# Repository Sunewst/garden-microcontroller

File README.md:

## Check the ESP32 C6 branch for the most up to date version

### Garden Microcontroller Arduino Library and Board https://github.com/Sunewst/garden-microcontroller-arduino

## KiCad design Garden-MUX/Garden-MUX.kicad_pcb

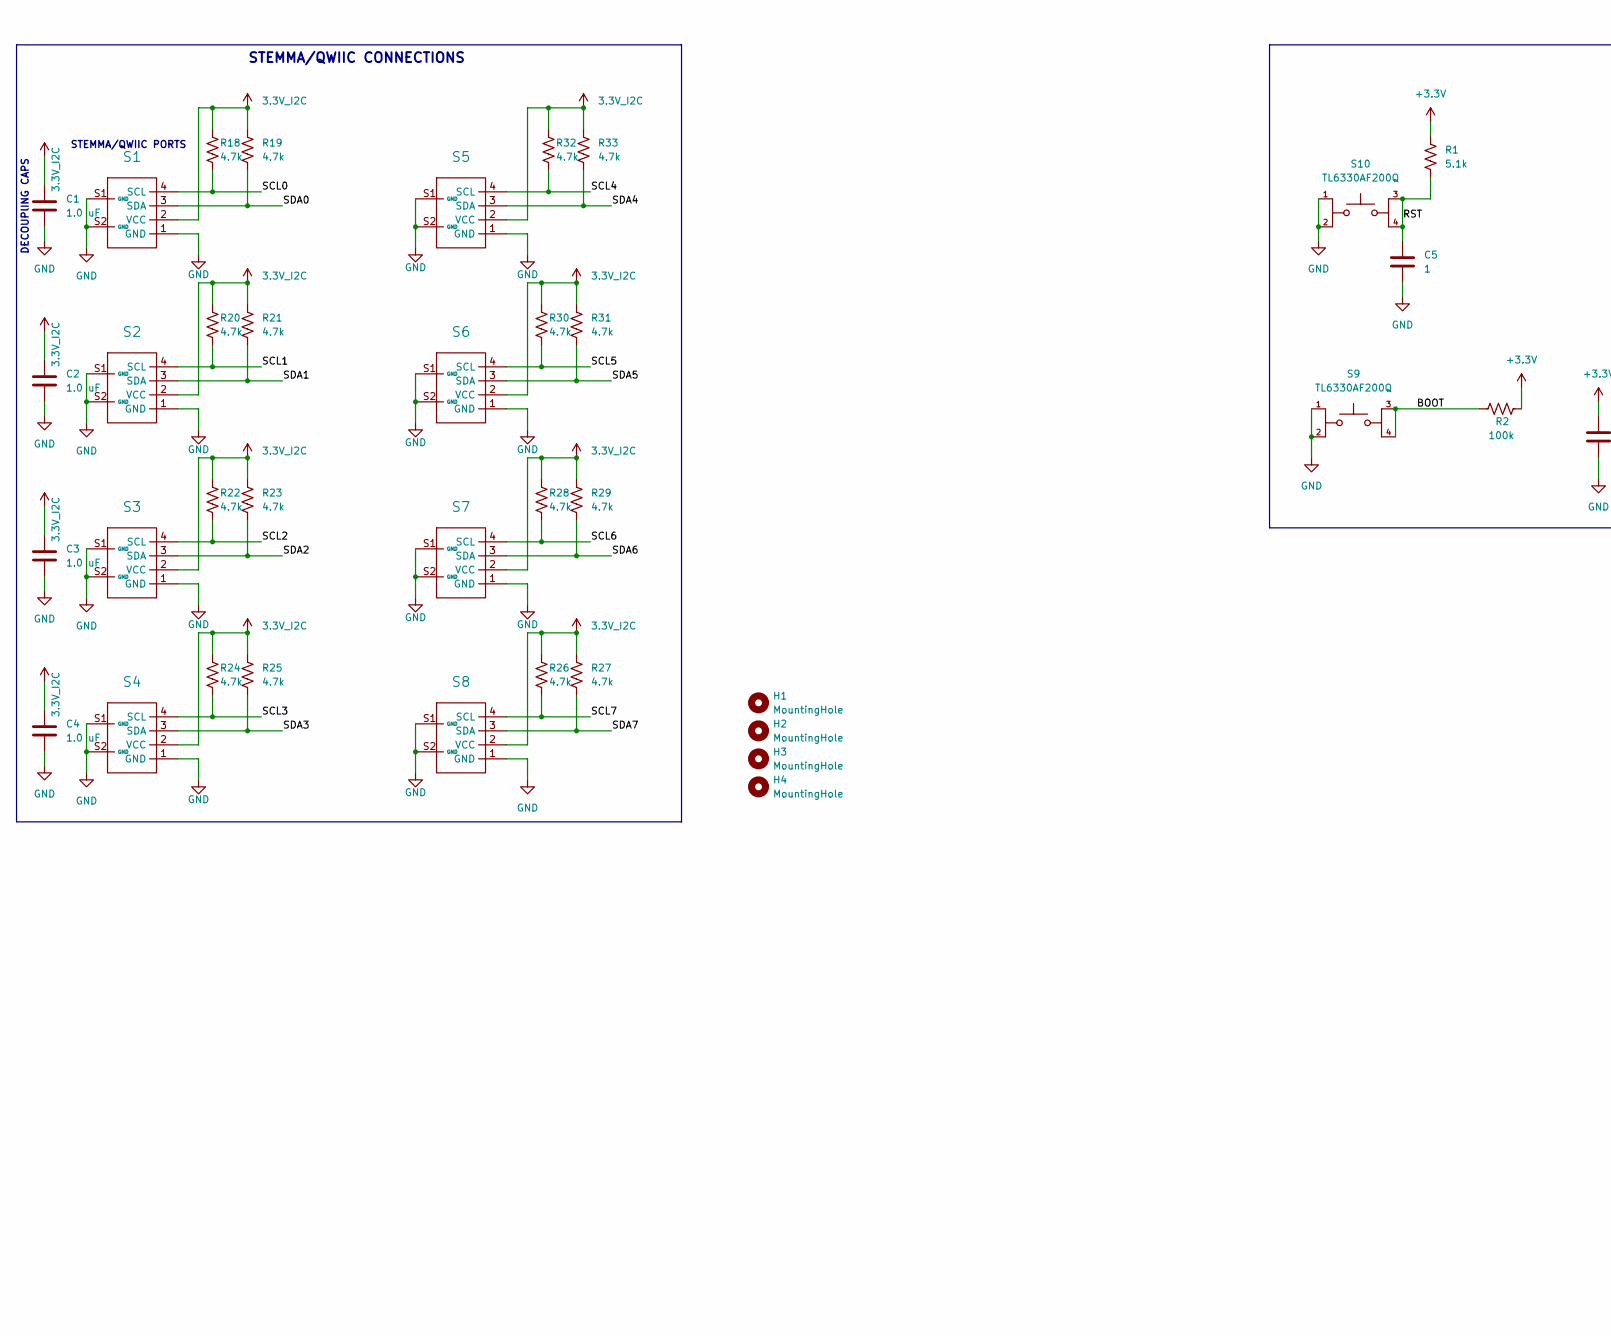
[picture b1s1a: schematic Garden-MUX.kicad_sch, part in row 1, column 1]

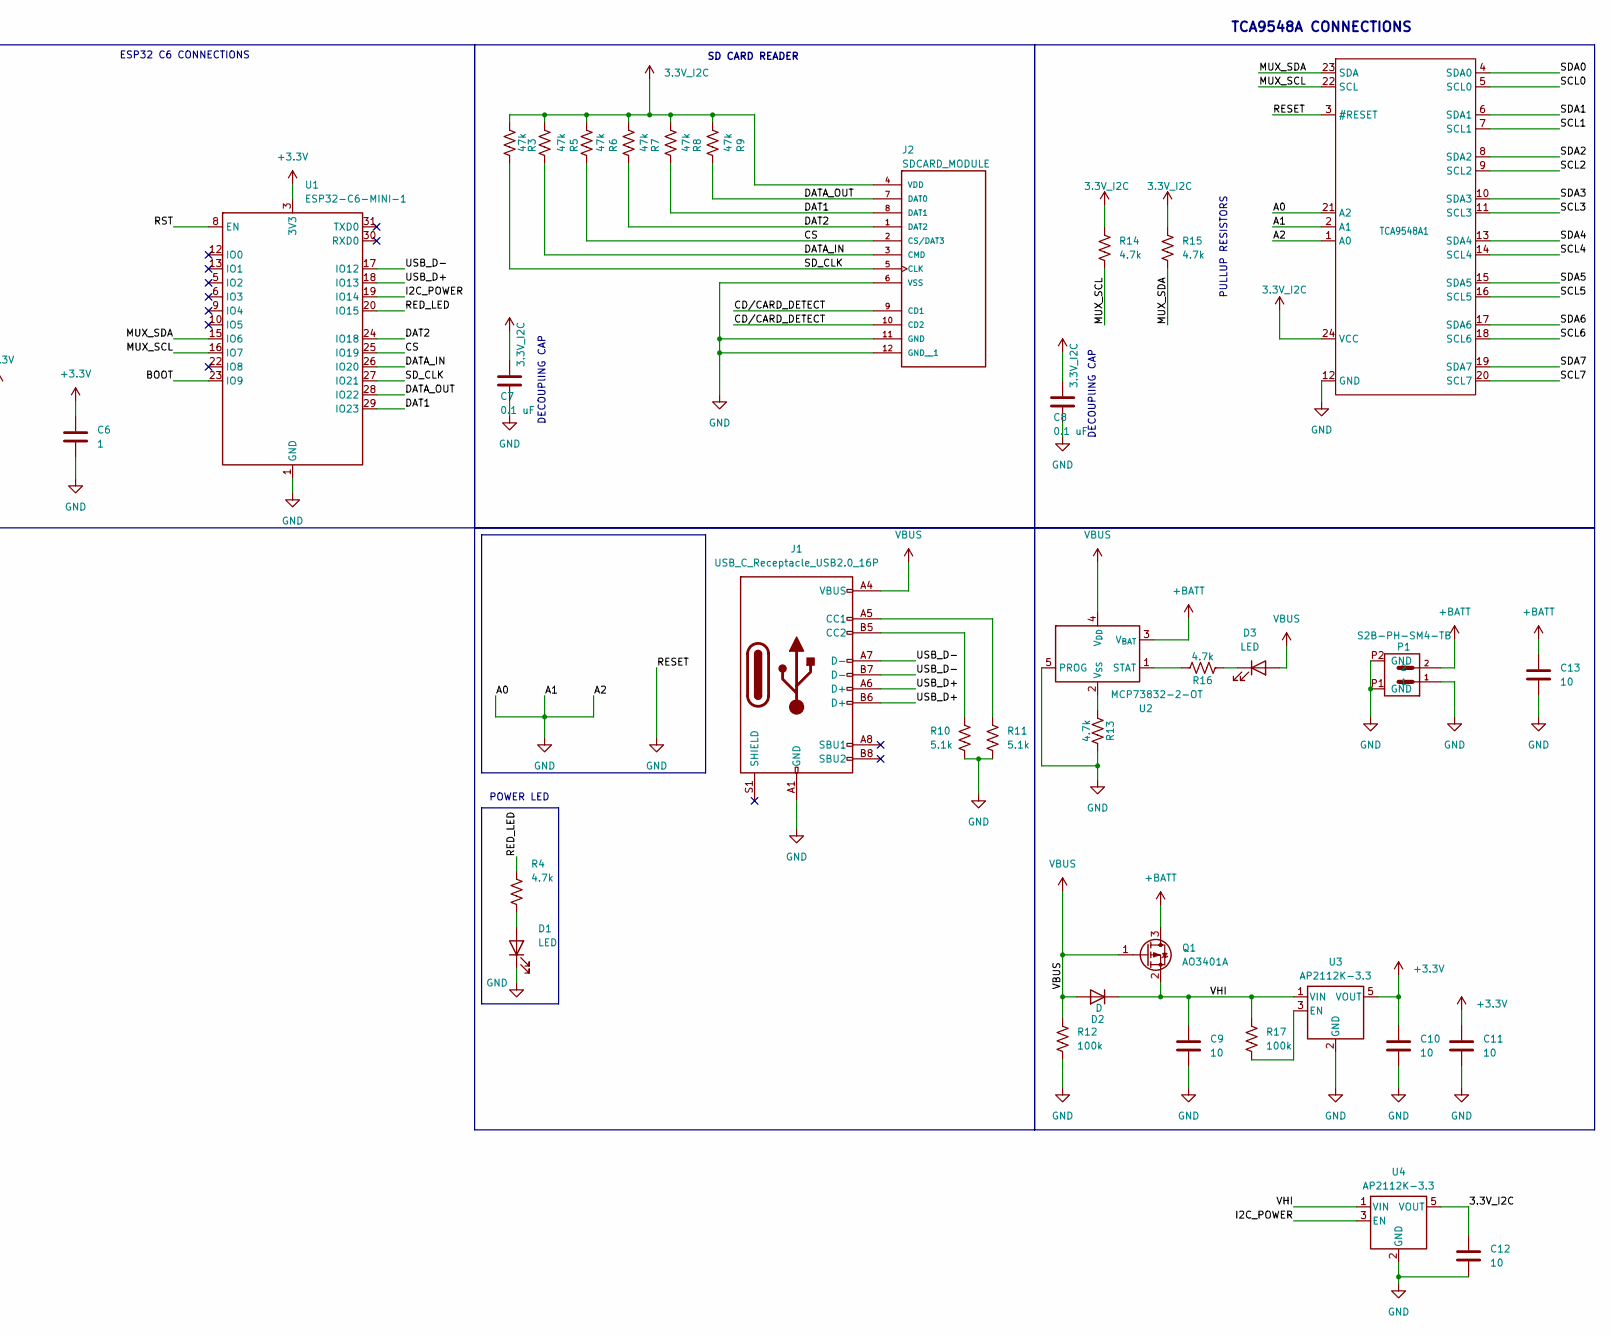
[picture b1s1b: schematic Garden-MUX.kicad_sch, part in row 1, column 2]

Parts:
C1, C2, C3, C4: 1.0 uF; C_0603_1608Metric
C5, C6: 1; C_0603_1608Metric
C7, C8: 0.1 uF; C_0603_1608Metric
C9, C10, C11, C12, C13: 10; C_0603_1608Metric
D1, D3: LED; LED_0603_1608Metric
D2: D; D_0402_1005Metric_Pad0.77x0.64mm_HandSolder
H1, H2, H3, H4: MountingHole; MountingHole_2.5mm
J1: USB_C_Receptacle_USB2.0_16P; USB_C_Receptacle_G-Switch_GT-USB-7010ASV
J2: SDCARD_MODULE; SDCARD_MODULE_Footprint
P1: S2B-PH-SM4-TB; JST_S2B-PH-SM4-TB
Q1: AO3401A; SOT-23
R1, R10, R11: 5.1k; R_0603_1608Metric
R2: 100k; R_0603_1608Metric
R3, R5, R6, R7, R8, R9: 47k; R_0603_1608Metric
R4, R13, R14, R15, R16, R18, R19, R20, R21, R22, R23, R24, R25, R26, R27, R28, R29, R30, R31, R32, R33: 4.7k; R_0603_1608Metric
R12, R17: 100k; R_0805_2012Metric
S1, S2, S3, S4, S5, S6, S7, S8: STEMMAQWIIC_Footprint
S9, S10: TL6330AF200Q; SW_TL6330AF200Q_Footprint; PARTREV D
TCA9548A1: TCA9548A_Footprint
U1: ESP32-C6-MINI-1
U2: MCP73832-2-OT; SOT-23-5
U3, U4: AP2112K-3.3; SOT-23-5

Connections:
3.3V_I2C: C1.1, C2.1, C3.1, C4.1, C7.1, C8.1, C12.1, J2.4 (VDD), R3.1, R5.1, R6.1, R7.1, R8.1, R9.1, R14.1, R15.1, R18.1, R19.1, R20.1, R21.1, R22.1, R23.1, R24.1, R25.1, R26.1, R27.1, R28.1, R29.1, R30.1, R31.1, R32.1, R33.1, S1.2 (VCC), S2.2 (VCC), S3.2 (VCC), S4.2 (VCC), S5.2 (VCC), S6.2 (VCC), S7.2 (VCC), S8.2 (VCC), TCA9548A1.24 (VCC), U4.5 (VOUT)
+3.3V: C6.1, C10.1, C11.1, R1.1, R2.1, U1.3 (3V3), U3.5 (VOUT)
+BATT: C13.1, P1.2, Q1.3 (D), U2.3 (V_{BAT})
/BOOT: R2.2, S9.3, S9.4, U1.23 (IO9)
/CD/CARD_DETECT: J2.9 (CD1), J2.10 (CD2)
/CS: J2.2 (CS/DAT3), R6.2, U1.25 (IO19)
/DAT1: J2.8 (DAT1), R8.2, U1.29 (IO23)
/DAT2: J2.1 (DAT2), R7.2, U1.24 (IO18)
/DATA_IN: J2.3 (CMD), R5.2, U1.26 (IO20)
/DATA_OUT: J2.7 (DAT0), R9.2, U1.28 (IO22)
/I2C_POWER: U1.19 (IO14), U4.3 (EN)
/MUX_SCL: R14.2, TCA9548A1.22 (SCL), U1.16 (IO7)
/MUX_SDA: R15.2, TCA9548A1.23 (SDA), U1.15 (IO6)
/RED_LED: R4.1, U1.20 (IO15)
/RST: C5.1, R1.2, S10.3, S10.4, U1.8 (EN)
/SCL0: R18.2, S1.4 (SCL), TCA9548A1.5 (SCL0)
/SCL1: R20.2, S2.4 (SCL), TCA9548A1.7 (SCL1)
/SCL2: R22.2, S3.4 (SCL), TCA9548A1.9 (SCL2)
/SCL3: R24.2, S4.4 (SCL), TCA9548A1.11 (SCL3)
/SCL4: R32.2, S5.4 (SCL), TCA9548A1.14 (SCL4)
/SCL5: R30.2, S6.4 (SCL), TCA9548A1.16 (SCL5)
/SCL6: R28.2, S7.4 (SCL), TCA9548A1.18 (SCL6)
/SCL7: R26.2, S8.4 (SCL), TCA9548A1.20 (SCL7)
/SDA0: R19.2, S1.3 (SDA), TCA9548A1.4 (SDA0)
/SDA1: R21.2, S2.3 (SDA), TCA9548A1.6 (SDA1)
/SDA2: R23.2, S3.3 (SDA), TCA9548A1.8 (SDA2)
/SDA3: R25.2, S4.3 (SDA), TCA9548A1.10 (SDA3)
/SDA4: R33.2, S5.3 (SDA), TCA9548A1.13 (SDA4)
/SDA5: R31.2, S6.3 (SDA), TCA9548A1.15 (SDA5)
/SDA6: R29.2, S7.3 (SDA), TCA9548A1.17 (SDA6)
/SDA7: R27.2, S8.3 (SDA), TCA9548A1.19 (SDA7)
/SD_CLK: J2.5 (CLK), R3.2, U1.27 (IO21)
/USB_D+: J1.A6 (D+), J1.B6 (D+), U1.18 (IO13)
/USB_D-: J1.A7 (D-), J1.B7 (D-), U1.17 (IO12)
/VHI: C9.1, D2.1 (K), Q1.2 (S), R17.1, U3.1 (VIN), U4.1 (VIN)
GND: C1.2, C2.2, C3.2, C4.2, C5.2, C6.2, C7.2, C8.2, C9.2, C10.2, C11.2, C12.2, C13.2, D1.1 (K), J1.A1 (GND), J1.A12 (GND), J1.B1 (GND), J1.B12 (GND), J2.6 (VSS), J2.11 (GND), J2.12 (GND__1), P1.1, P1.P1 (GND), P1.P2 (GND), R10.2, R11.2, R12.2, R13.1, S1.1 (GND), S1.S1 (GND), S1.S2 (GND), S2.1 (GND), S2.S1 (GND), S2.S2 (GND), S3.1 (GND), S3.S1 (GND), S3.S2 (GND), S4.1 (GND), S4.S1 (GND), S4.S2 (GND), S5.1 (GND), S5.S1 (GND), S5.S2 (GND), S6.1 (GND), S6.S1 (GND), S6.S2 (GND), S7.1 (GND), S7.S1 (GND), S7.S2 (GND), S8.1 (GND), S8.S1 (GND), S8.S2 (GND), S9.1, S9.2, S10.1, S10.2, TCA9548A1.1 (A0), TCA9548A1.2 (A1), TCA9548A1.3 (#RESET), TCA9548A1.12 (GND), TCA9548A1.21 (A2), U1.1 (GND), U1.2 (GND), U1.11 (GND), U1.14 (GND), U1.36 (GND), U1.37 (GND), U1.38 (GND), U1.39 (GND), U1.40 (GND), U1.41 (GND), U1.42 (GND), U1.43 (GND), U1.44 (GND), U1.45 (GND), U1.46 (GND), U1.47 (GND), U1.48 (GND), U1.49 (GND), U1.50 (GND), U1.51 (GND), U1.52 (GND), U1.53 (GND), U2.5 (PROG), U3.2 (GND), U4.2 (GND)
unnamed: D1.2 (A), R4.2
unnamed: D3.1 (K), R16.2
unnamed: J1.A5 (CC1), R11.1
unnamed: J1.B5 (CC2), R10.1
unnamed: R16.1, U2.1 (STAT)
unnamed: R13.2, U2.2 (V_{SS})
unnamed: R17.2, U3.3 (EN)
VBUS: D2.2 (A), D3.2 (A), J1.A4 (VBUS), J1.A9 (VBUS), J1.B4 (VBUS), J1.B9 (VBUS), Q1.1 (G), R12.1, U2.4 (V_{DD})

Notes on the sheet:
POWER LED
STEMMA/QWIIC CONNECTIONS
PULLUP RESISTORS
STEMMA/QWIIC PORTS
SD CARD READER
DECOUPlING CAPS
DECOUPlING CAP
ESP32 C6 CONNECTIONS
TCA9548A CONNECTIONS

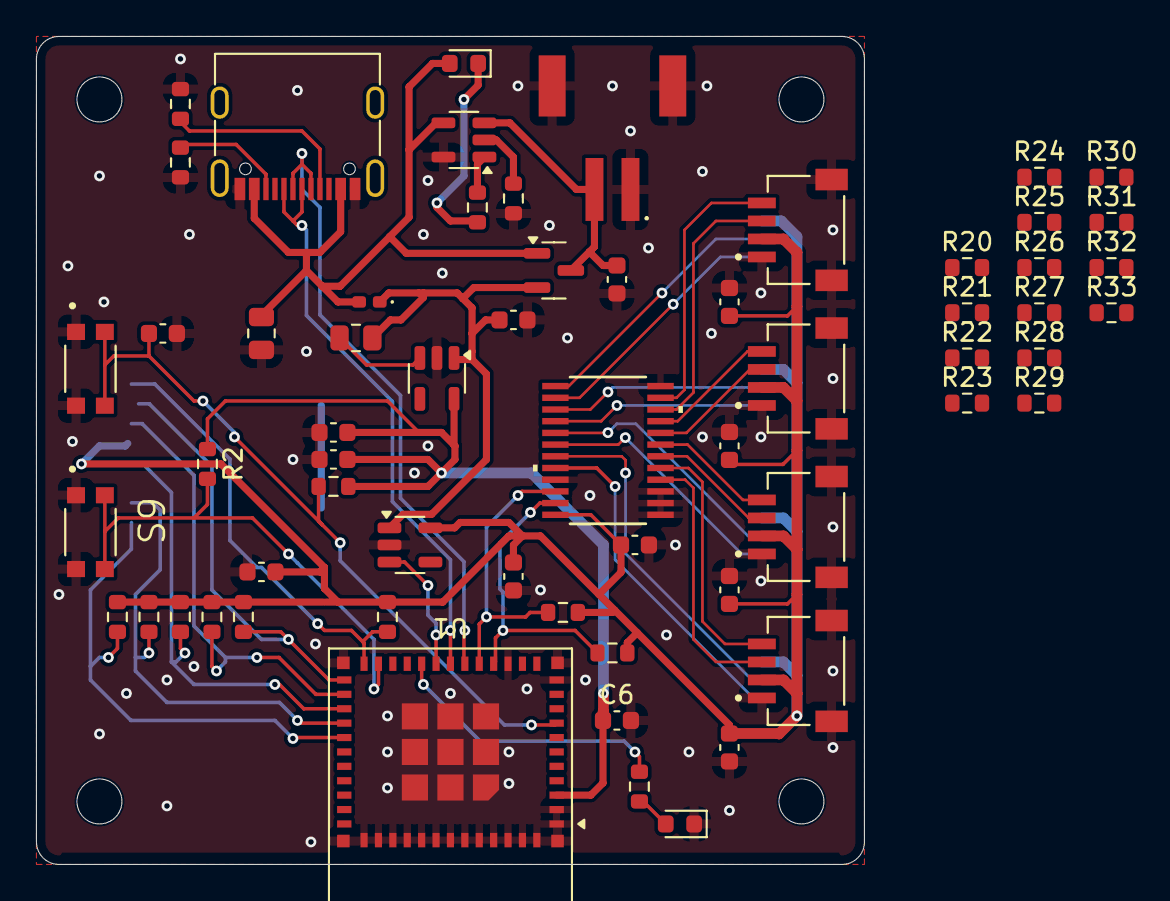
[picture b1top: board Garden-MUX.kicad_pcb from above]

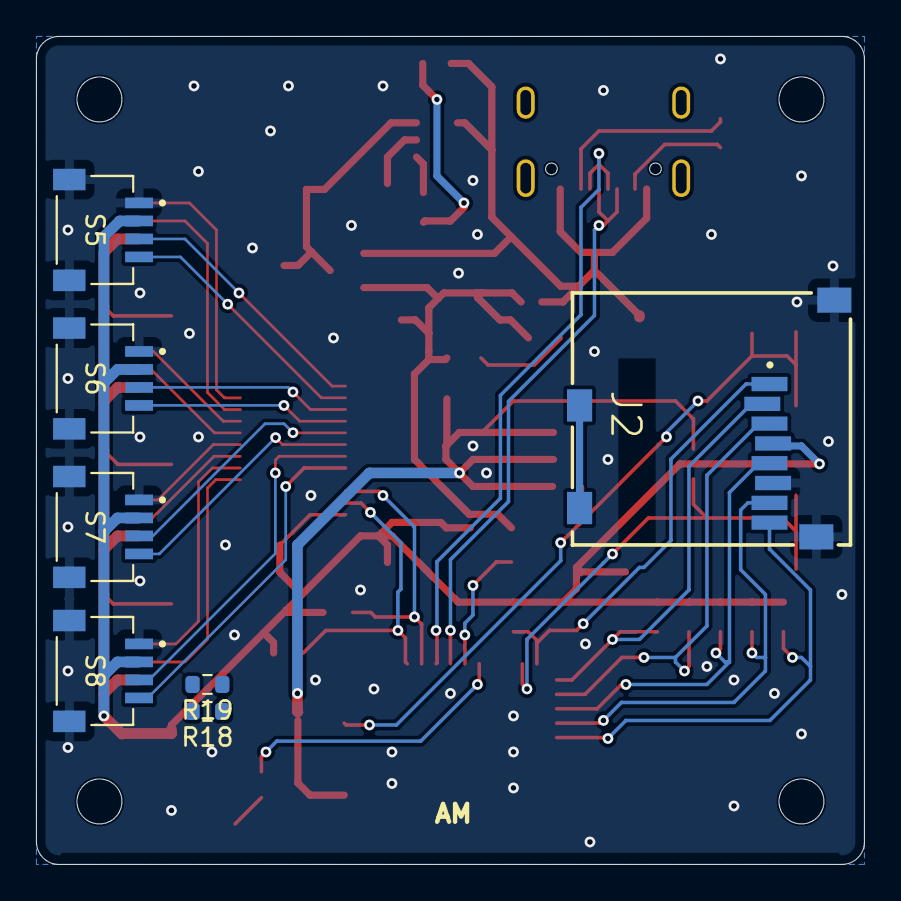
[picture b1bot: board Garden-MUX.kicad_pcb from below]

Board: 2 copper layers, 46.0 x 46.0 mm, 72 parts (7 on the bottom side), 44 nets.

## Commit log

2025-06-14 initial changes
2025-06-16 Add missing May changes
2025-06-16 Fix footprint warnings
2025-06-17 adjust power traces width
    change from 0.6 mm to 0.4 mm
2025-06-17 Transfer capacitors from 4 layer board
2025-06-19 Update 3D models file locations to global
    The 3D models file paths no longer need to modified to be seen
2025-06-20 change esp32 power trace
2025-06-24 Add boot button and adjust 3D models
2025-06-24 Add name silkscreen
2025-08-13 Adjust GND via placement
2025-09-08 Adjust position of 3d models
2025-09-14 Switch red LED to IO15
2025-09-16 Add USB-C 3D model
2025-09-16 Delete .DS_Store
    Delete Garden-MUX/.DS_Store
2025-09-23 Move decaps and resistors to the left
    Start the process of moving 3.3v components further to the right to allow room for pull-up resistors.
2026-03-08 Update assembly pdf
